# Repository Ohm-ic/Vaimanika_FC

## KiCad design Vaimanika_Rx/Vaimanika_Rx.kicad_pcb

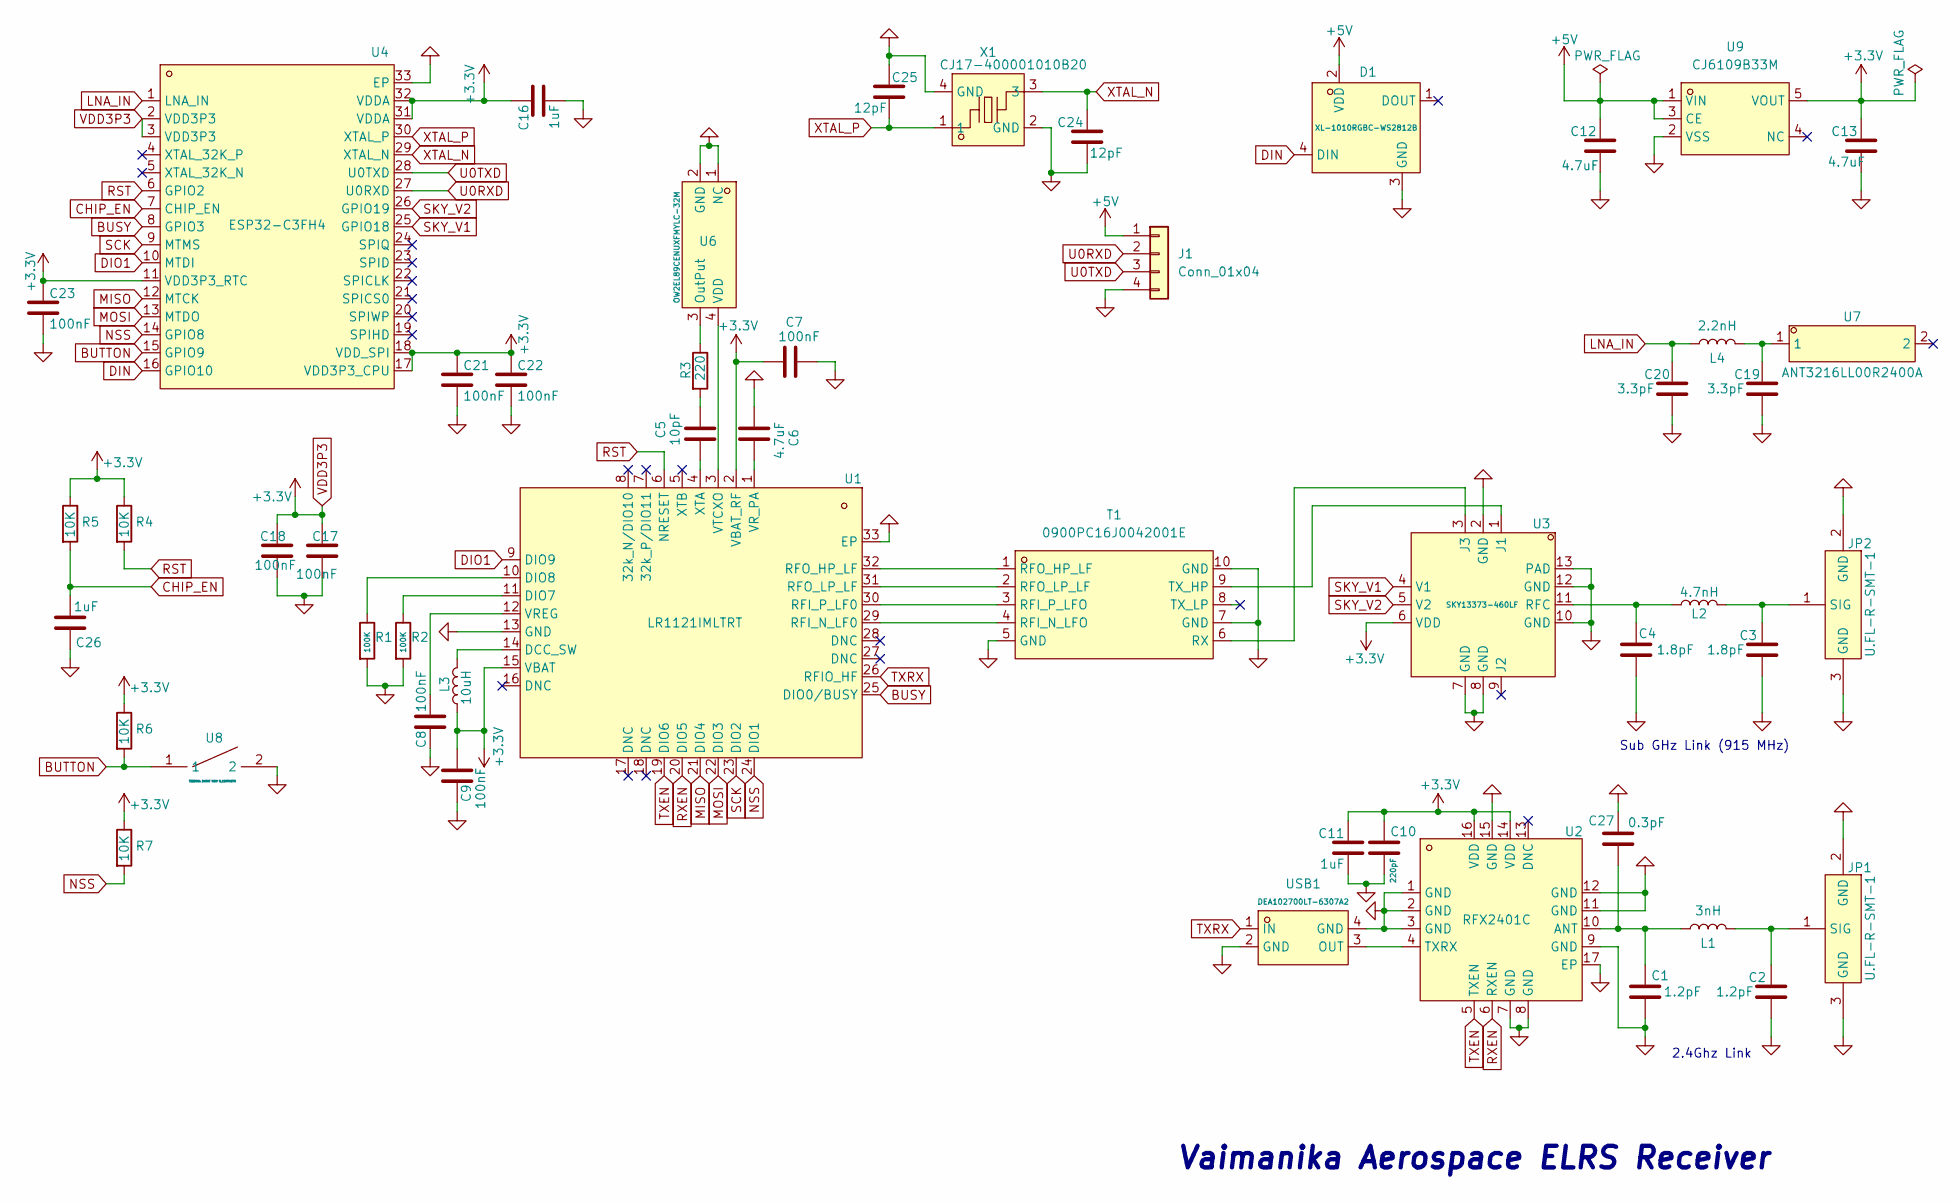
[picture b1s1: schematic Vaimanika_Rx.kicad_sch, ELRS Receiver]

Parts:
C1, C2: 1.2pF; C_0402_1005Metric; LCSC C5186867
C3, C4: 1.8pF; C_0402_1005Metric; LCSC C301970
C5: 10pF; C_0402_1005Metric; LCSC C513681
C6: 4.7uF; C_0402_1005Metric; LCSC C33595851
C7, C8, C9, C17, C18, C21, C22, C23: 100nF; C_0402_1005Metric; LCSC C60474
C10: 220pF; C_0402_1005Metric; LCSC C597026
C11, C16, C26: 1uF; C_0402_1005Metric; LCSC C5137474
C12, C13: 4.7uF; C_0402_1005Metric; LCSC C22399610
C19, C20: 3.3pF; C_0402_1005Metric; LCSC C5448815
C24, C25: 12pF; C_0402_1005Metric; LCSC C106201
C27: 0.3pF; C_0402_1005Metric; LCSC C1870422
D1: XL-1010RGBC-WS2812B; LED-SMD_4P-L1.0-W1.0-TL_XL-1010RGBC-WS2812B; MPN XL-1010RGBC-2812B; LCSC C5349953
J1: Conn_01x04; Rec_Conn_01x04
JP1, JP2: U.FL-R-SMT-1; RF-SMD_FRF05002-JSS103M; MPN U.FL-R-SMT-1(80); LCSC C88374
L1: 3nH; L_0402_1005Metric; LCSC C269824
L2: 4.7nH; L_0402_1005Metric; LCSC C167480
L3: 10uH; L_0603_1608Metric; LCSC C194437
L4: 2.2nH; L_0402_1005Metric; LCSC C97985
R1, R2: 100K; R_0402_1005Metric; LCSC C60491
R3: 220; R_0402_1005Metric; LCSC C112291
R4, R5, R6, R7: 10K; R_0402_1005Metric; LCSC C22404129
T1: 0900PC16J0042001E; FILTER-SMD_10P-L2.0-W1.6-BL; MPN 0900PC16J0042001E; LCSC C19842466
U1: LR1121IMLTRT; QFN-32_L5.0-W5.0-P0.50-BL-EP3.7; MPN LR1121IMLTRT; LCSC C7498014
U2: RFX2401C; QFN-16_L3.0-W3.0-P0.50-BL-EP1.7; MPN RFX2401C; LCSC C19213
U3: SKY13373-460LF; QFN-12_L2.0-W2.0-P0.50-BL-EP; MPN SKY13373-460LF; LCSC C150853
U4: ESP32-C3FH4; QFN-32_L5.0-W5.0-P0.50-BL-EP3.7; MPN ESP32-C3FH4; LCSC C2858491
U6: OW2EL89CENUXFMYLC-32M; OSC-SMD_4P-L3.2-W2.5-BL; MPN OW2EL89CENUXFMYLC-32M; LCSC C22434888
U7: ANT3216LL00R2400A; ANT-SMD_L3.2-W1.6; MPN ANT3216LL00R2400A; LCSC C293767
U8: TS2306A 240GF MSM 9_C2976675; SW-SMD_4P-L3.0-W2.0-P0.85-LS3.5; MPN TS2306A 240gf MSM 9; LCSC C2976675
U9: CJ6109B33M; SOT-23-5_L2.9-W1.6-P0.95-LS2.8-BR; MPN CJ6109B33M; LCSC C17703066
USB1: DEA102700LT-6307A2; FILTER-SMD_4P-L1.0-W0.5-L_DEA102700LT-XXX; MPN DEA102700LT-6307A2; LCSC C574024
X1: CJ17-400001010B20; CRYSTAL-SMD_4P-L1.6-W1.2-BL; MPN CJ17-400001010B20; LCSC C2875272

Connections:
+5V: C12.1, D1.2 (VDD), J1.1, U9.1 (VIN), U9.3 (CE)
BUSY: U1.25 (DIO0/BUSY), U4.8 (GPIO3)
BUTTON: R6.2, U4.15 (GPIO9), U8.1
CHIP_EN: C26.2, R5.2, U4.7 (CHIP_EN)
DIN: D1.4 (DIN), U4.16 (GPIO10)
DIO1: U1.9 (DIO9), U4.10 (MTDI)
GND: C1.2, C2.2, C3.2, C4.2, C6.2, C7.1, C8.2, C9.2, C10.2, C11.2, C12.2, C13.2, C16.2, C17.2, C18.2, C19.2, C20.2, C21.2, C22.2, C23.2, C24.2, C25.1, C26.1, C27.1, D1.3 (GND), J1.4, JP1.2 (GND), JP1.3 (GND), JP2.2 (GND), JP2.3 (GND), R1.2, R2.2, T1.5 (GND), T1.7 (GND), T1.10 (GND), U1.13 (GND), U1.33 (EP), U2.1 (GND), U2.2 (GND), U2.3 (GND), U2.7 (GND), U2.8 (GND), U2.9 (GND), U2.11 (GND), U2.12 (GND), U2.15 (GND), U2.17 (EP), U3.2 (GND), U3.7 (GND), U3.8 (GND), U3.10 (GND), U3.12 (GND), U3.13 (PAD), U4.33 (EP), U6.1 (NC), U6.2 (GND), U8.2, U9.2 (VSS), USB1.2 (GND), USB1.4 (GND), X1.2 (GND), X1.4 (GND)
LNA_IN: C20.1, L4.1, U4.1 (LNA_IN)
MISO: U1.21 (DIO4), U4.12 (MTCK)
MOSI: U1.22 (DIO3), U4.13 (MTDO)
NSS: R7.2, U1.24 (DIO1), U4.14 (GPIO8)
unnamed: C5.1, R3.2
unnamed: C19.1, L4.2, U7.1
unnamed: C2.1, JP1.1 (SIG), L1.2
unnamed: C3.1, JP2.1 (SIG), L2.2
unnamed: T1.4 (RFI_N_LFO), U1.29 (RFI_N_LF0)
unnamed: T1.3 (RFI_P_LFO), U1.30 (RFI_P_LF0)
unnamed: T1.1 (RFO_HP_LF), U1.32 (RFO_HP_LF)
unnamed: T1.2 (RFO_LP_LF), U1.31 (RFO_LP_LF)
unnamed: T1.6 (RX), U3.3 (J3)
unnamed: T1.9 (TX_HP), U3.1 (J1)
unnamed: L3.2, U1.14 (DCC_SW)
unnamed: R2.1, U1.11 (DIO7)
unnamed: R1.1, U1.10 (DIO8)
unnamed: C8.1, U1.12 (VREG)
unnamed: C6.1, U1.1 (VR_PA)
unnamed: U1.3 (VTCXO), U6.4 (VDD)
unnamed: C5.2, U1.4 (XTA)
unnamed: C1.1, C27.2, L1.1, U2.10 (ANT)
unnamed: U2.4 (TXRX), USB1.3 (OUT)
unnamed: C4.1, L2.1, U3.11 (RFC)
unnamed: R3.1, U6.3 (OutPut)
RST: R4.2, U1.6 (NRESET), U4.6 (GPIO2)
RXEN: U1.20 (DIO5), U2.6 (RXEN)
SCK: U1.23 (DIO2), U4.9 (MTMS)
SKY_V1: U3.4 (V1), U4.25 (GPIO18)
SKY_V2: U3.5 (V2), U4.26 (GPIO19)
TXEN: U1.19 (DIO6), U2.5 (TXEN)
TXRX: U1.26 (RFIO_HF), USB1.1 (IN)
U0RXD: J1.2, U4.27 (U0RXD)
U0TXD: J1.3, U4.28 (U0TXD)
VDD3P3: C7.2, C9.1, C10.1, C11.1, C13.1, C16.1, C17.1, C18.1, C21.1, C22.1, C23.1, L3.1, R4.1, R5.1, R6.1, R7.1, U1.2 (VBAT_RF), U1.15 (VBAT), U2.14 (VDD), U2.16 (VDD), U3.6 (VDD), U4.2 (VDD3P3), U4.3 (VDD3P3), U4.11 (VDD3P3_RTC), U4.17 (VDD3P3_CPU), U4.18 (VDD_SPI), U4.31 (VDDA), U4.32 (VDDA), U9.5 (VOUT)
XTAL_N: C24.1, U4.29 (XTAL_N), X1.3
XTAL_P: C25.2, U4.30 (XTAL_P), X1.1

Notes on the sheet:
2.4Ghz Link
Sub GHz Link (915 MHz)
Vaimanika Aerospace ELRS Receiver

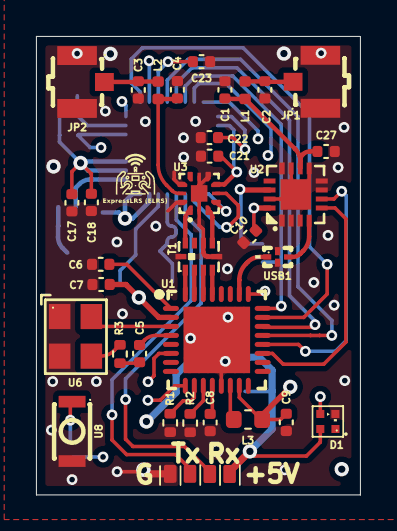
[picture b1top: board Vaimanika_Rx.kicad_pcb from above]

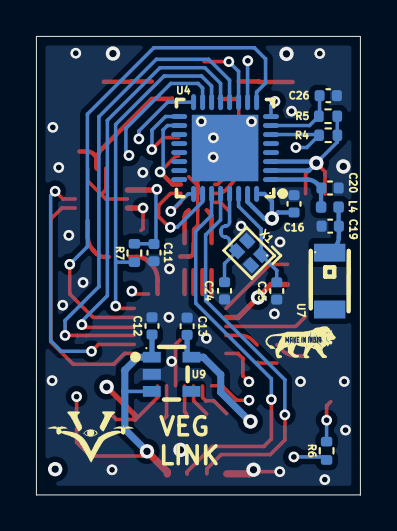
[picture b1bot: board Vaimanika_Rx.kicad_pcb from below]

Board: 4 copper layers, 18.0 x 25.5 mm, 51 parts (18 on the bottom side), 44 nets.

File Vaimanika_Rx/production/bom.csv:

Designator,Footprint,Quantity,Value,LCSC Part #
"C1, C2",0402,2,1.2pF,C5186867
C10,0402,1,220pF,C597026
"C11, C16, C26",0402,3,1uF,C5137474
"C12, C13",0402,2,4.7uF,C22399610
"C17, C18, C21, C22, C23, C7, C8, C9",0402,8,100nF,C60474
"C19, C20",0402,2,3.3pF,C5448815
"C24, C25",0402,2,12pF,C106201
C27,0402,1,0.3pF,C1870422
"C3, C4",0402,2,1.8pF,C301970
C5,0402,1,10pF,C513681
C6,0402,1,4.7uF,C33595851
D1,LED-SMD_4P-L1.0-W1.0-TL_XL-1010RGBC-WS2812B,1,XL-1010RGBC-WS2812B,C5349953
"JP1, JP2",RF-SMD_FRF05002-JSS103M,2,U.FL-R-SMT-1,C88374
L1,0402,1,3nH,C269824
L2,0402,1,4.7nH,C167480
L3,0603,1,10uH,C194437
L4,0402,1,2.2nH,C97985
"R1, R2",0402,2,100K,C60491
R3,0402,1,220,C112291
"R4, R5, R6, R7",0402,4,10K,C22404129
T1,FILTER-SMD_10P-L2.0-W1.6-BL,1,0900PC16J0042001E,C19842466
U1,QFN-32_L5.0-W5.0-P0.50-BL-EP3.7,1,LR1121IMLTRT,C7498014
U2,QFN-16_L3.0-W3.0-P0.50-BL-EP1.7,1,RFX2401C,C19213
U3,QFN-12_L2.0-W2.0-P0.50-BL-EP,1,SKY13373-460LF,C150853
U4,QFN-32_L5.0-W5.0-P0.50-BL-EP3.7,1,ESP32-C3FH4,C7498014
U6,OSC-SMD_4P-L3.2-W2.5-BL,1,OW2EL89CENUXFMYLC-32M,C22434888
U7,ANT-SMD_L3.2-W1.6,1,ANT3216LL00R2400A,C293767
U8,SW-SMD_4P-L3.0-W2.0-P0.85-LS3.5,1,TS2306A 240GF MSM 9_C2976675,C2976675
U9,SOT-23-5_L2.9-W1.6-P0.95-LS2.8-BR,1,CJ6109B33M,C17703066
USB1,FILTER-SMD_4P-L1.0-W0.5-L_DEA102700LT-XXX,1,DEA102700LT-6307A2,C574024
X1,CRYSTAL-SMD_4P-L1.6-W1.2-BL,1,CJ17-400001010B20,C2875272

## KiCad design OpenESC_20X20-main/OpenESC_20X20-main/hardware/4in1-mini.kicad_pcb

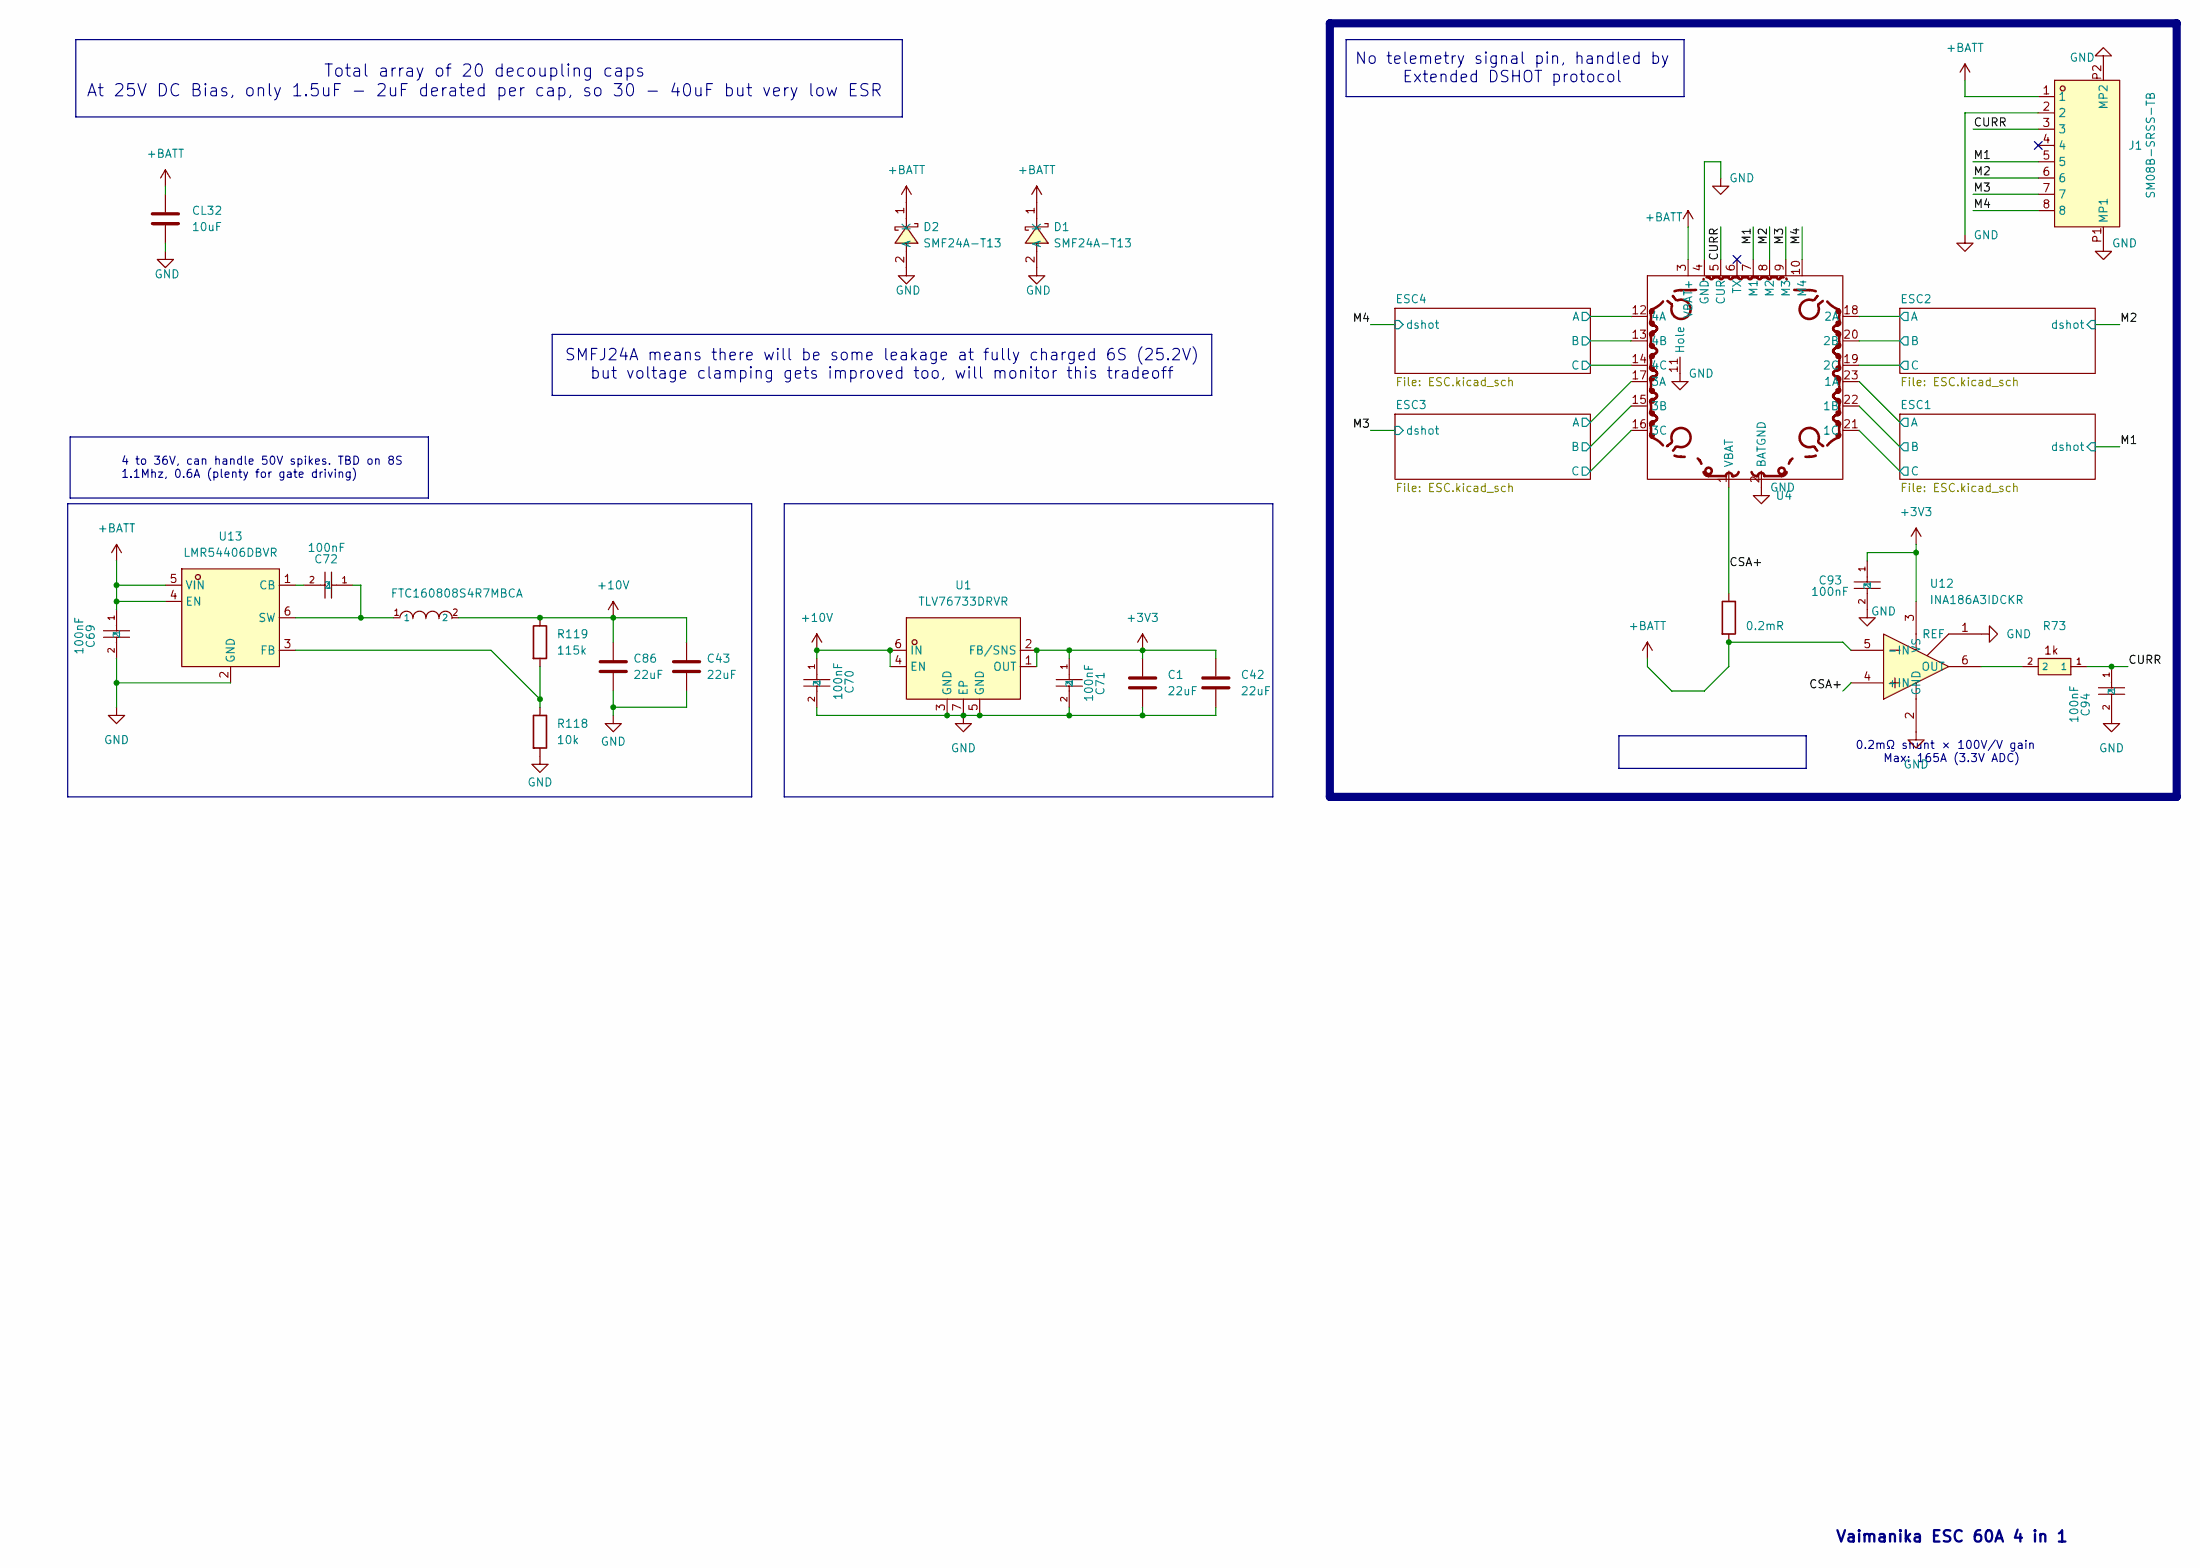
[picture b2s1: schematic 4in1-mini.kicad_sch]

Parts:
C1, C42: 22uF; C_0402_1005Metric; MPN CL05A226MQ5QUNC; LCSC C105226
C43, C86: 22uF; C_0603_1608Metric; MPN CL10A226MO7JZNC; LCSC C2762594
C69, C70, C71, C72, C93, C94: 100nF; C_0201_0603Metric; MPN GRM033R6YA104KE14D; LCSC C181043
CL32: 10uF; C_1206_3216Metric; MPN CL31B106KBHNNNE; LCSC C89632
D1, D2: SMF24A-T13; SOD-123FL_L2.7-W1.8-LS3.7-RD; MPN SMF24A-T13; LCSC Part C1977154
J1: SM08B-SRSS-TB; JST_SM08B-SRSS-TB; MPN SM08B-SRSS-TB(LF)(SN); LCSC C160407
R73: 1k; R_0201_0603Metric; MPN 0201WMF1001TEE; LCSC C270365
R118: 10k; R_0201_0603Metric; MPN RC0201FR-0710KL; LCSC C106225
R119: 115k; R_0201_0603Metric; MPN RTT011153FTH; LCSC C166378
Rsense1: 0.2mR; R_2512_6332Metric; MPN ASR-S-3-0.2F; LCSC C695806
U1: TLV76733DRVR; WSON-6_L2.0-W2.0-P0.65-TL-EP; MPN TLV76733DRVR; LCSC C2848334
U4: 4in1ESC
U5: FTC160808S4R7MBCA; IND-SMD_L1.6-W0.8_FTC160865SR47MBCA; MPN FTC160808S4R7MBCA; LCSC C46594347
U12: INA186A3IDCKR; SOT-363_SC-70-6; MPN INA186A3IDCKR; LCSC C2058245
U13: LMR54406DBVR; SOT-23-6_L2.9-W1.6-P0.95-LS2.8-BR; MPN LMR54406DBVR; LCSC Part C5219316

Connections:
+3V3: C1.2, C42.2, C71.1, C93.1, U1.1 (OUT), U1.2 (FB/SNS), U12.3 (VS); also elsewhere on the board
+10V: C43.1, C70.1, C86.1, R119.1, U1.4 (EN), U1.6 (IN), U5.2; also elsewhere on the board
+BATT: C69.1, CL32.1, D1.1 (K), D2.1 (K), J1.1, Rsense1.2, U4.3 (VBAT+), U12.5 (-IN), U13.4 (EN), U13.5 (VIN); also elsewhere on the board
/CSA+: Rsense1.1, U4.1 (VBAT), U12.4 (+IN)
/CURR: C94.1, J1.3, R73.1, U4.5 (CUR)
/ESC1/MotorA: U4.23 (1A); also elsewhere on the board
/ESC1/MotorB: U4.22 (1B); also elsewhere on the board
/ESC1/MotorC: U4.21 (1C); also elsewhere on the board
/ESC2/MotorA: U4.18 (2A); also elsewhere on the board
/ESC2/MotorB: U4.20 (2B); also elsewhere on the board
/ESC2/MotorC: U4.19 (2C); also elsewhere on the board
/ESC3/MotorA: U4.17 (3A); also elsewhere on the board
/ESC3/MotorB: U4.15 (3B); also elsewhere on the board
/ESC3/MotorC: U4.16 (3C); also elsewhere on the board
/ESC4/MotorA: U4.12 (4A); also elsewhere on the board
/ESC4/MotorB: U4.13 (4B); also elsewhere on the board
/ESC4/MotorC: U4.14 (4C); also elsewhere on the board
/M1: J1.5, U4.7 (M1); also elsewhere on the board
/M2: J1.6, U4.8 (M2); also elsewhere on the board
/M3: J1.7, U4.9 (M3); also elsewhere on the board
/M4: J1.8, U4.10 (M4); also elsewhere on the board
GND: C1.1, C42.1, C43.2, C69.2, C70.2, C71.2, C86.2, C93.2, C94.2, CL32.2, D1.2 (A), D2.2 (A), J1.2, J1.P1 (MP1), J1.P2 (MP2), R118.2, U1.3 (GND), U1.5 (GND), U1.7 (EP), U4.2 (BATGND), U4.4 (GND), U4.11 (Hole), U12.1 (REF), U12.2 (GND), U13.2 (GND); also elsewhere on the board
unnamed: R73.2, U12.6 (OUT)
unnamed: C72.2, U13.1 (CB)
unnamed: R118.1, R119.2, U13.3 (FB)
unnamed: C72.1, U5.1, U13.6 (SW)

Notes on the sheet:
No telemetry signal pin, handled by Extended DSHOT protocol
4 to 36V, can handle 50V spikes. TBD on 8S 1.1Mhz, 0.6A (plenty for gate driving)
SMFJ24A means there will be some leakage at fully charged 6S (25.2V) but voltage clamping gets improved too, will monitor this tradeoff
Vaimanika ESC 60A 4 in 1
Total array of 20 decoupling caps At 25V DC Bias, only 1.5uF - 2uF derated per cap, so 30 - 40uF but very low ESR
0.2mΩ shunt × 100V/V gain Max: 165A (3.3V ADC)

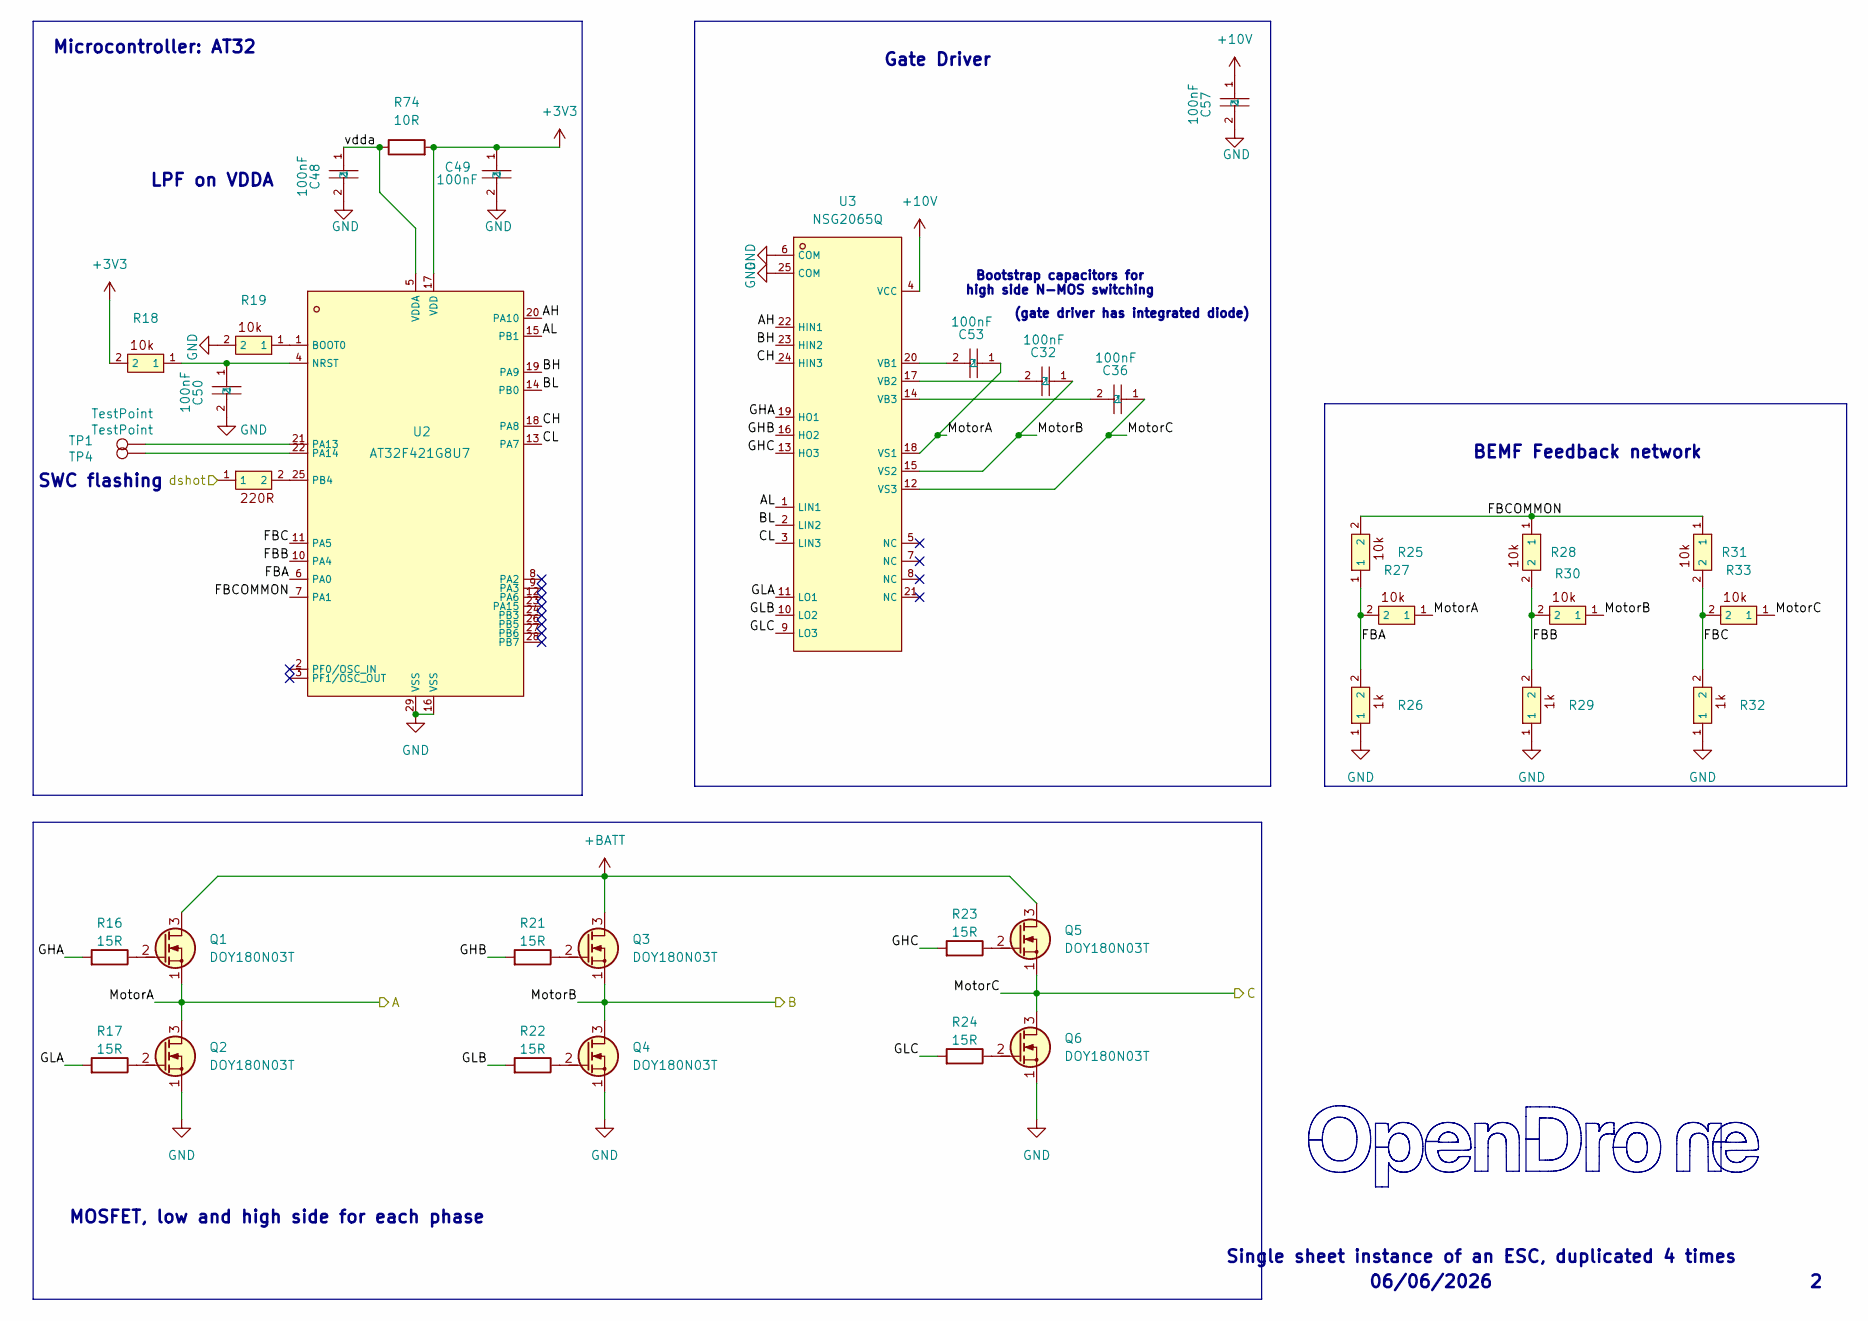
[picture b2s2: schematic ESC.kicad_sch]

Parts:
C32, C36, C53: 100nF; C_0402_WIDE; MPN CL05B104KB54PNC; LCSC C307331
C48, C49, C50, C57: 100nF; C_0201_0603Metric; MPN GRM033R6YA104KE14D; LCSC C181043
Q1, Q2, Q3, Q4, Q5, Q6: DOY180N03T; Diodes_PowerDI3333-8; MPN DOY180N03T; LCSC C49441966
R16, R17, R21, R22, R23, R24: 15R; R_0201_0603Metric; MPN 0201WMF150JTEE; LCSC C473542
R18, R19, R25, R27, R28, R30, R31, R33: 10k; R_0201_0603Metric; MPN RC0201FR-0710KL; LCSC C106225
R20: 220R; R_0201_0603Metric; MPN AC0201FR-07220RL; LCSC C226468
R26, R29, R32: 1k; R_0201_0603Metric; MPN 0201WMF1001TEE; LCSC C270365
R74: 10R; R_0201_0603Metric; MPN RC0201FR-0710RL; LCSC C106226
TP1, TP4: TestPoint; TestPoint_Pad_D1.0mm
U2: AT32F421G8U7; QFN-28_L4.0-W4.0-P0.40-TL-EP2.4; MPN AT32F421G8U7; LCSC C2765098
U3: NSG2065Q; QFN-24_L4.0-W4.0-P0.50-TL-EP2.8; MPN NSG2065Q; LCSC C41414478

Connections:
+3V3: C49.1, R18.2, R74.2, U2.17 (VDD); also elsewhere on the board
+10V: C57.1, U3.4 (VCC); also elsewhere on the board
+BATT: Q1.3 (D), Q3.3 (D), Q5.3 (D); also elsewhere on the board
/ESC1/AH: U2.20 (PA10), U3.22 (HIN1)
/ESC1/AL: U2.15 (PB1), U3.1 (LIN1)
/ESC1/BH: U2.19 (PA9), U3.23 (HIN2)
/ESC1/BL: U2.14 (PB0), U3.2 (LIN2)
/ESC1/CH: U2.18 (PA8), U3.24 (HIN3)
/ESC1/CL: U2.13 (PA7), U3.3 (LIN3)
/ESC1/FBA: R25.1, R26.2, R27.2, U2.6 (PA0)
/ESC1/FBB: R28.2, R29.2, R30.2, U2.10 (PA4)
/ESC1/FBC: R31.2, R32.2, R33.2, U2.11 (PA5)
/ESC1/FBCOMMON: R25.2, R28.1, R31.1, U2.7 (PA1)
/ESC1/GHA: R16.1, U3.19 (HO1)
/ESC1/GHB: R21.1, U3.16 (HO2)
/ESC1/GHC: R23.1, U3.13 (HO3)
/ESC1/GLA: R17.1, U3.11 (LO1)
/ESC1/GLB: R22.1, U3.10 (LO2)
/ESC1/GLC: R24.1, U3.9 (LO3)
/ESC1/MotorA: C53.1, Q1.1 (S), Q2.3 (D), R27.1, U3.18 (VS1); also elsewhere on the board
/ESC1/MotorB: C32.1, Q3.1 (S), Q4.3 (D), R30.1, U3.15 (VS2); also elsewhere on the board
/ESC1/MotorC: C36.1, Q5.1 (S), Q6.3 (D), R33.1, U3.12 (VS3); also elsewhere on the board
/ESC1/vdda: C48.1, R74.1, U2.5 (VDDA)
/M1: R20.1; also elsewhere on the board
GND: C48.2, C49.2, C50.2, C57.2, Q2.1 (S), Q4.1 (S), Q6.1 (S), R19.2, R26.1, R29.1, R32.1, U2.16 (VSS), U2.29 (VSS), U3.6 (COM), U3.25 (COM); also elsewhere on the board
unnamed: Q1.2 (G), R16.2
unnamed: Q2.2 (G), R17.2
unnamed: Q3.2 (G), R21.2
unnamed: Q4.2 (G), R22.2
unnamed: Q5.2 (G), R23.2
unnamed: Q6.2 (G), R24.2
unnamed: R19.1, U2.1 (BOOT0)
unnamed: C50.1, R18.1, U2.4 (NRST)
unnamed: TP1.1 (1_1), U2.21 (PA13)
unnamed: TP4.1 (1_1), U2.22 (PA14)
unnamed: R20.2, U2.25 (PB4)
unnamed: C53.2, U3.20 (VB1)
unnamed: C32.2, U3.17 (VB2)
unnamed: C36.2, U3.14 (VB3)

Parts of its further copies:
C33, C34, C35, C37, C38, C39, C59, C73, C83: 100nF; C_0402_WIDE; MPN CL05B104KB54PNC; LCSC C307331
C44, C45, C46, C63, C64, C65, C66, C77, C78, C79, C80, C88: 100nF; C_0201_0603Metric; MPN GRM033R6YA104KE14D; LCSC C181043
Q7, Q8, Q9, Q10, Q11, Q12, Q13, Q14, Q15, Q16, Q17, Q18, Q19, Q20, Q21, Q22, Q23, Q24: DOY180N03T; Diodes_PowerDI3333-8; MPN DOY180N03T; LCSC C49441966
R1, R2, R6, R7, R8, R9, R37, R38, R42, R43, R44, R45, R55, R56, R60, R61, R62, R63: 15R; R_0201_0603Metric; MPN 0201WMF150JTEE; LCSC C473542
R3, R4, R10, R12, R13, R15, R34, R36, R39, R40, R46, R48, R49, R51, R52, R54, R57, R58, R64, R66, R67, R69, R70, R72: 10k; R_0201_0603Metric; MPN RC0201FR-0710KL; LCSC C106225
R5, R41, R59: 220R; R_0201_0603Metric; MPN AC0201FR-07220RL; LCSC C226468
R11, R14, R35, R47, R50, R53, R65, R68, R71: 1k; R_0201_0603Metric; MPN 0201WMF1001TEE; LCSC C270365
R75, R76, R77: 10R; R_0201_0603Metric; MPN RC0201FR-0710RL; LCSC C106226
TP2, TP3, TP5, TP6, TP7, TP8: TestPoint; TestPoint_Pad_D1.0mm
U6, U8, U10: AT32F421G8U7; QFN-28_L4.0-W4.0-P0.40-TL-EP2.4; MPN AT32F421G8U7; LCSC C2765098
U7, U9, U11: NSG2065Q; QFN-24_L4.0-W4.0-P0.50-TL-EP2.8; MPN NSG2065Q; LCSC C41414478

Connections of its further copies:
+3V3: C45.1, C65.1, C79.1, R3.2, R39.2, R57.2, R75.2, R76.2, R77.2, U6.17 (VDD), U8.17 (VDD), U10.17 (VDD); also elsewhere on the board
+10V: C63.1, C77.1, C88.1, U7.4 (VCC), U9.4 (VCC), U11.4 (VCC); also elsewhere on the board
+BATT: Q7.3 (D), Q9.3 (D), Q11.3 (D), Q13.3 (D), Q15.3 (D), Q17.3 (D), Q19.3 (D), Q21.3 (D), Q23.3 (D); also elsewhere on the board
/ESC2/AH: U6.20 (PA10), U7.22 (HIN1)
/ESC2/AL: U6.15 (PB1), U7.1 (LIN1)
/ESC2/BH: U6.19 (PA9), U7.23 (HIN2)
/ESC2/BL: U6.14 (PB0), U7.2 (LIN2)
/ESC2/CH: U6.18 (PA8), U7.24 (HIN3)
/ESC2/CL: U6.13 (PA7), U7.3 (LIN3)
/ESC2/FBA: R10.1, R11.2, R12.2, U6.6 (PA0)
/ESC2/FBB: R13.2, R14.2, R15.2, U6.10 (PA4)
/ESC2/FBC: R34.2, R35.2, R36.2, U6.11 (PA5)
/ESC2/FBCOMMON: R10.2, R13.1, R34.1, U6.7 (PA1)
/ESC2/GHA: R1.1, U7.19 (HO1)
/ESC2/GHB: R6.1, U7.16 (HO2)
/ESC2/GHC: R8.1, U7.13 (HO3)
/ESC2/GLA: R2.1, U7.11 (LO1)
/ESC2/GLB: R7.1, U7.10 (LO2)
/ESC2/GLC: R9.1, U7.9 (LO3)
/ESC2/MotorA: C59.1, Q7.1 (S), Q8.3 (D), R12.1, U7.18 (VS1); also elsewhere on the board
/ESC2/MotorB: C33.1, Q9.1 (S), Q10.3 (D), R15.1, U7.15 (VS2); also elsewhere on the board
/ESC2/MotorC: C37.1, Q11.1 (S), Q12.3 (D), R36.1, U7.12 (VS3); also elsewhere on the board
/ESC2/vdda: C44.1, R75.1, U6.5 (VDDA)
/ESC3/AH: U8.20 (PA10), U9.22 (HIN1)
/ESC3/AL: U8.15 (PB1), U9.1 (LIN1)
/ESC3/BH: U8.19 (PA9), U9.23 (HIN2)
/ESC3/BL: U8.14 (PB0), U9.2 (LIN2)
/ESC3/CH: U8.18 (PA8), U9.24 (HIN3)
/ESC3/CL: U8.13 (PA7), U9.3 (LIN3)
/ESC3/FBA: R46.1, R47.2, R48.2, U8.6 (PA0)
/ESC3/FBB: R49.2, R50.2, R51.2, U8.10 (PA4)
/ESC3/FBC: R52.2, R53.2, R54.2, U8.11 (PA5)
/ESC3/FBCOMMON: R46.2, R49.1, R52.1, U8.7 (PA1)
/ESC3/GHA: R37.1, U9.19 (HO1)
/ESC3/GHB: R42.1, U9.16 (HO2)
/ESC3/GHC: R44.1, U9.13 (HO3)
/ESC3/GLA: R38.1, U9.11 (LO1)
/ESC3/GLB: R43.1, U9.10 (LO2)
/ESC3/GLC: R45.1, U9.9 (LO3)
/ESC3/MotorA: C73.1, Q13.1 (S), Q14.3 (D), R48.1, U9.18 (VS1); also elsewhere on the board
/ESC3/MotorB: C34.1, Q15.1 (S), Q16.3 (D), R51.1, U9.15 (VS2); also elsewhere on the board
/ESC3/MotorC: C38.1, Q17.1 (S), Q18.3 (D), R54.1, U9.12 (VS3); also elsewhere on the board
/ESC3/vdda: C64.1, R76.1, U8.5 (VDDA)
/ESC4/AH: U10.20 (PA10), U11.22 (HIN1)
/ESC4/AL: U10.15 (PB1), U11.1 (LIN1)
/ESC4/BH: U10.19 (PA9), U11.23 (HIN2)
/ESC4/BL: U10.14 (PB0), U11.2 (LIN2)
/ESC4/CH: U10.18 (PA8), U11.24 (HIN3)
/ESC4/CL: U10.13 (PA7), U11.3 (LIN3)
/ESC4/FBA: R64.1, R65.2, R66.2, U10.6 (PA0)
/ESC4/FBB: R67.2, R68.2, R69.2, U10.10 (PA4)
/ESC4/FBC: R70.2, R71.2, R72.2, U10.11 (PA5)
/ESC4/FBCOMMON: R64.2, R67.1, R70.1, U10.7 (PA1)
/ESC4/GHA: R55.1, U11.19 (HO1)
/ESC4/GHB: R60.1, U11.16 (HO2)
/ESC4/GHC: R62.1, U11.13 (HO3)
/ESC4/GLA: R56.1, U11.11 (LO1)
/ESC4/GLB: R61.1, U11.10 (LO2)
/ESC4/GLC: R63.1, U11.9 (LO3)
/ESC4/MotorA: C83.1, Q19.1 (S), Q20.3 (D), R66.1, U11.18 (VS1); also elsewhere on the board
/ESC4/MotorB: C35.1, Q21.1 (S), Q22.3 (D), R69.1, U11.15 (VS2); also elsewhere on the board
/ESC4/MotorC: C39.1, Q23.1 (S), Q24.3 (D), R72.1, U11.12 (VS3); also elsewhere on the board
/ESC4/vdda: C78.1, R77.1, U10.5 (VDDA)
/M2: R5.1; also elsewhere on the board
/M3: R41.1; also elsewhere on the board
/M4: R59.1; also elsewhere on the board
GND: C44.2, C45.2, C46.2, C63.2, C64.2, C65.2, C66.2, C77.2, C78.2, C79.2, C80.2, C88.2, Q8.1 (S), Q10.1 (S), Q12.1 (S), Q14.1 (S), Q16.1 (S), Q18.1 (S), Q20.1 (S), Q22.1 (S), Q24.1 (S), R4.2, R11.1, R14.1, R35.1, R40.2, R47.1, R50.1, R53.1, R58.2, R65.1, R68.1, R71.1, U6.16 (VSS), U6.29 (VSS), U7.6 (COM), U7.25 (COM), U8.16 (VSS), U8.29 (VSS), U9.6 (COM), U9.25 (COM), U10.16 (VSS), U10.29 (VSS), U11.6 (COM), U11.25 (COM); also elsewhere on the board
unnamed: Q7.2 (G), R1.2
unnamed: Q8.2 (G), R2.2
unnamed: Q9.2 (G), R6.2
unnamed: Q10.2 (G), R7.2
unnamed: Q11.2 (G), R8.2
unnamed: Q12.2 (G), R9.2
unnamed: Q13.2 (G), R37.2
unnamed: Q14.2 (G), R38.2
unnamed: Q15.2 (G), R42.2
unnamed: Q16.2 (G), R43.2
unnamed: Q17.2 (G), R44.2
unnamed: Q18.2 (G), R45.2
unnamed: Q19.2 (G), R55.2
unnamed: Q20.2 (G), R56.2
unnamed: Q21.2 (G), R60.2
unnamed: Q22.2 (G), R61.2
unnamed: Q23.2 (G), R62.2
unnamed: Q24.2 (G), R63.2
unnamed: R4.1, U6.1 (BOOT0)
unnamed: C46.1, R3.1, U6.4 (NRST)
unnamed: TP2.1 (1_1), U6.21 (PA13)
unnamed: TP3.1 (1_1), U6.22 (PA14)
unnamed: R5.2, U6.25 (PB4)
unnamed: C59.2, U7.20 (VB1)
unnamed: C33.2, U7.17 (VB2)
unnamed: C37.2, U7.14 (VB3)
unnamed: R40.1, U8.1 (BOOT0)
unnamed: C66.1, R39.1, U8.4 (NRST)
unnamed: TP5.1 (1_1), U8.21 (PA13)
unnamed: TP6.1 (1_1), U8.22 (PA14)
unnamed: R41.2, U8.25 (PB4)
unnamed: C73.2, U9.20 (VB1)
unnamed: C34.2, U9.17 (VB2)
unnamed: C38.2, U9.14 (VB3)
unnamed: R58.1, U10.1 (BOOT0)
unnamed: C80.1, R57.1, U10.4 (NRST)
unnamed: TP7.1 (1_1), U10.21 (PA13)
unnamed: TP8.1 (1_1), U10.22 (PA14)
unnamed: R59.2, U10.25 (PB4)
unnamed: C83.2, U11.20 (VB1)
unnamed: C35.2, U11.17 (VB2)
unnamed: C39.2, U11.14 (VB3)

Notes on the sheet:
Bootstrap capacitors for high side N-MOS switching
Gate Driver
MOSFET, low and high side for each phase
Single sheet instance of an ESC, duplicated 4 times
Microcontroller: AT32
SWC flashing
(gate driver has integrated diode)
06/06/2026
BEMF Feedback network
LPF on VDDA

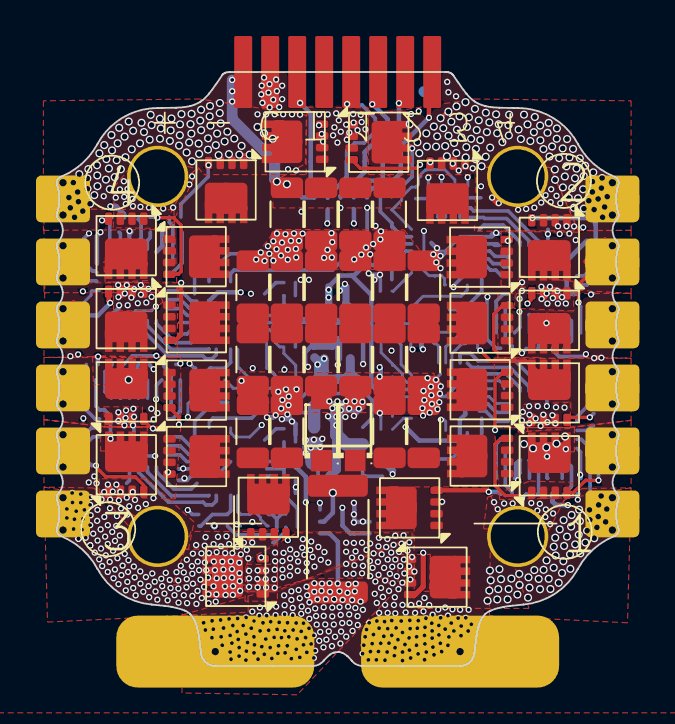
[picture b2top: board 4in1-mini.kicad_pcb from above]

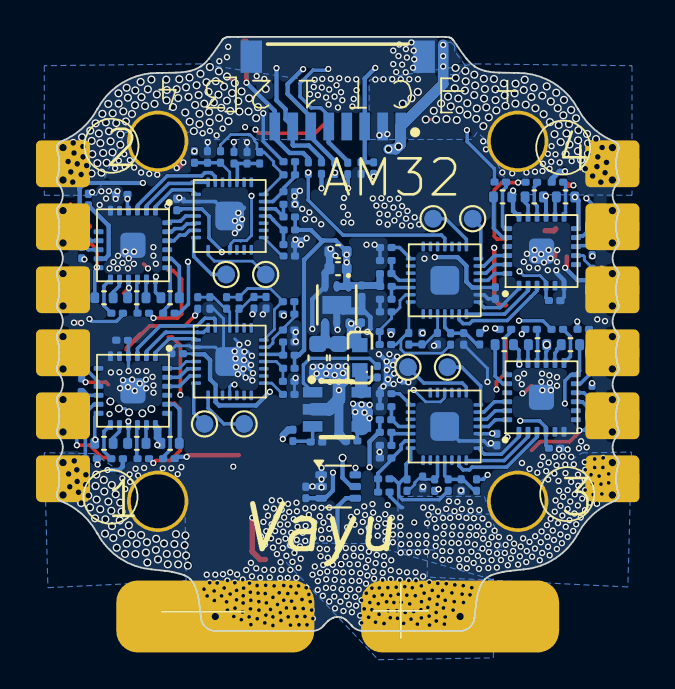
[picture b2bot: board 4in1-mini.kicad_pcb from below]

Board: 6 copper layers, 31.2 x 33.0 mm, 186 parts (138 on the bottom side), 150 nets.

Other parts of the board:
CL33, CL34, CL35, CL36, CL38, CL39, CL40, CL42, CL43, CL44, CL45, CL46, CL47, CL48, CL49, CL50, CL51, CL54, CL55: 10uF; C_1206_3216Metric

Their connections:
+BATT: CL33.1, CL34.1, CL35.1, CL36.1, CL38.1, CL39.1, CL40.1, CL42.1, CL43.1, CL44.1, CL45.1, CL46.1, CL47.1, CL48.1, CL49.1, CL50.1, CL51.1, CL54.1, CL55.1; also elsewhere on the board
GND: CL33.2, CL34.2, CL35.2, CL36.2, CL38.2, CL39.2, CL40.2, CL42.2, CL43.2, CL44.2, CL45.2, CL46.2, CL47.2, CL48.2, CL49.2, CL50.2, CL51.2, CL54.2, CL55.2; also elsewhere on the board
